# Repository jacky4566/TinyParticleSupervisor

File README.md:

# TinyParticleSupervisor
Using an ATTINYx4 with SpenceKonde/ATTinyCore to control the enable pin on a 3rd gen particle.io board.
Keeps Real Time for only 6uA around 100ppm or worse.  
ATTINY simulates I2C for two registers and controls a wake pin according to internal timers. 

# Wiring
| Pin Mode      | Function                    | Core Pin | ATTINYx4 PIN  |
| ------------- | -------------               | :--------: | :------------: |
| OUTPUT        | Control Particle EN pin     |    1     | PA1           |
| INPUT         | Detect if Particle is awake |    2     | PA2           |
| INPUT         | I2C SDA                     |    6     | PA6           |
| INPUT         | I2C SCL                     |    4     | P4           |

# Registers
All registers read and write 32 bit

I2C Address = 0x07

unixTimeRegister 0x01 (Increaments at 1HZ from WDT)

wakeTimeRegister 0x02

# TODO:
- Add defines to support both ATTINYx5 and ATTINYx4
- Investigate alternate chips, ATtiny13A , perhaps STM32L0 for lower run power, RTC crystal, Proper I2C
- Add function to read VCC for boards without Power Good Signal

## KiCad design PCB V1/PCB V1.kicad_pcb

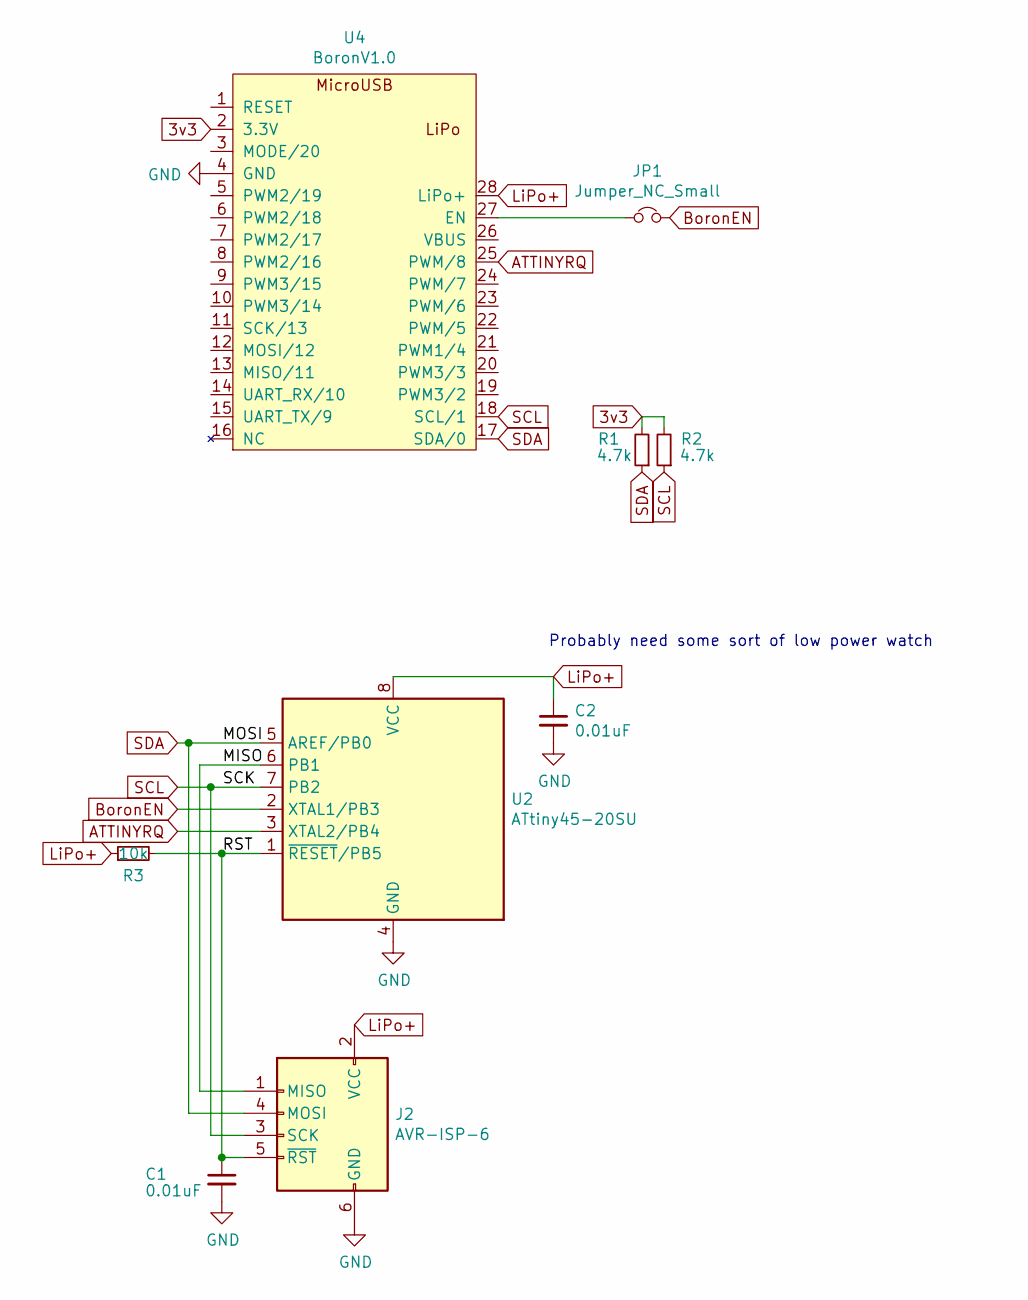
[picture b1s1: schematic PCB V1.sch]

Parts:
C1, C2: 0.01uF; C_0603_1608Metric
J2: AVR-ISP-6; PinHeader_2x03_P2.54mm_Vertical
JP1: Jumper_NC_Small; SolderJumper-2_P1.3mm_Open_Pad1.0x1.5mm
R1, R2: 4.7k; R_0603_1608Metric
R3: 10k; R_0603_1608Metric
U2: ATtiny45-20SU; SOIJ-8_5.3x5.3mm_P1.27mm
U4: BoronV1.0

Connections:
3v3: R1.2, R2.2, U4.2 (3.3V)
/MISO: J2.1 (MISO), U2.6 (PB1)
/RST: C1.1, J2.5 (~RST), R3.2, U2.1 (~RESET~/PB5)
ATTINYRQ: U2.3 (XTAL2/PB4), U4.25 (PWM/8)
BoronEN: JP1.2, U2.2 (XTAL1/PB3)
GND: C1.2, C2.2, J2.6 (GND), U2.4 (GND), U4.4 (GND)
LiPo+: C2.1, J2.2 (VCC), R3.1, U2.8 (VCC), U4.28 (LiPo+)
unnamed: JP1.1, U4.27 (EN)
SCL: J2.3 (SCK), R2.1, U2.7 (PB2), U4.18 (SCL/1)
SDA: J2.4 (MOSI), R1.1, U2.5 (AREF/PB0), U4.17 (SDA/0)

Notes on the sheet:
Probably need some sort of low power watch

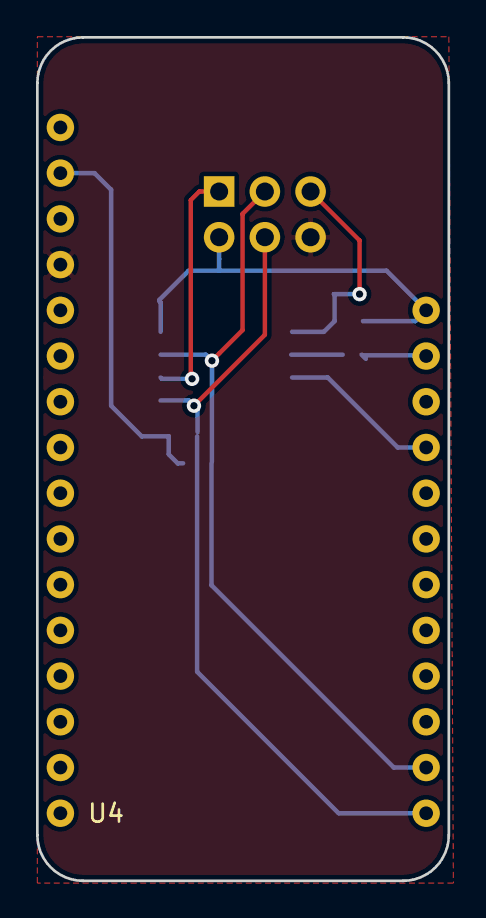
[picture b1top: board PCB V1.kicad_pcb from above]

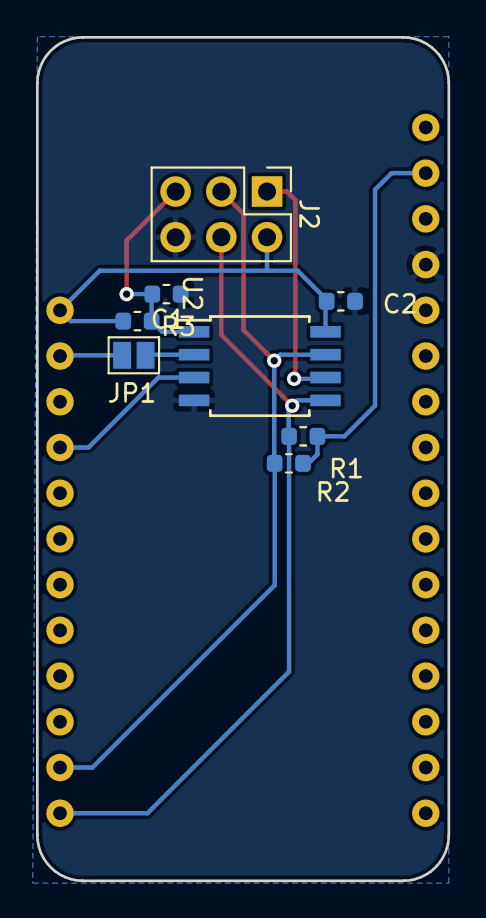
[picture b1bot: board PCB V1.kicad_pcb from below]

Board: 2 copper layers, 22.9 x 46.9 mm, 9 parts (8 on the bottom side), 10 nets.

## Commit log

2019-09-27 Rename TinyBoronSupervisor.ino to TinyParticleSupervisor.ino
2019-09-27 Add PCBv1
2019-09-27 Updates to pcb
2019-09-27 Remove Particle extras
2019-09-27 Added project foorprints
2019-10-08 Move to Folder
2019-10-11 Wrote library
2020-01-13 update working version
2020-03-09 Update for ATTINYx4
    Consistant code!
2020-03-09 lines
2020-03-09 Killer bullet points
